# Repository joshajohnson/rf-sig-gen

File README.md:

# RF Signal Generator

## 23.5 - 6000 MHz MAX2871 based RF signal generator in an Adafruit Feather form factor.
- MAX2871 23.5 - 6000 MHz Fractional/Integer-N Synthesizer/VCO
- -35 to +15 dBm output power (-25 to +10 across entire frequency range)
- Output control within 0.5 dB, with closed loop feedback
- GUI allowing easy control, including sweep capabilities
- Adafruit Feather form factor
- Firmware works with my [STM32F103 Feather](https://github.com/joshajohnson/stm32f103-feather)

### TODO

#### Software
- [ ] Display not updating if time between frequency steps in sweep is too long (greater than UART timeout)
- [ ] Map keyboard to frequency and power adjustment in GUI
- [ ] CLI and GUI modes based on sys.argv **NOTE CLI works but is very finiky wrt command order and updating**
- [ ] Fractional vs Int N selection

#### Firmware
- [ ] Calibrate output power
- [ ] Rewrite with RTOS to ensure a more responsive user experience
- [ ] Add ability to select Frac / Int N PLL settings
- [ ] Dimmable LEDs

#### Hardware
- [ ] Many pin locations incorrect (SPI pins off by one...)
- [ ] LED's back to front, and connected to GND instead of VCC
- [ ] Feather footprint internal pin numbers incorrect

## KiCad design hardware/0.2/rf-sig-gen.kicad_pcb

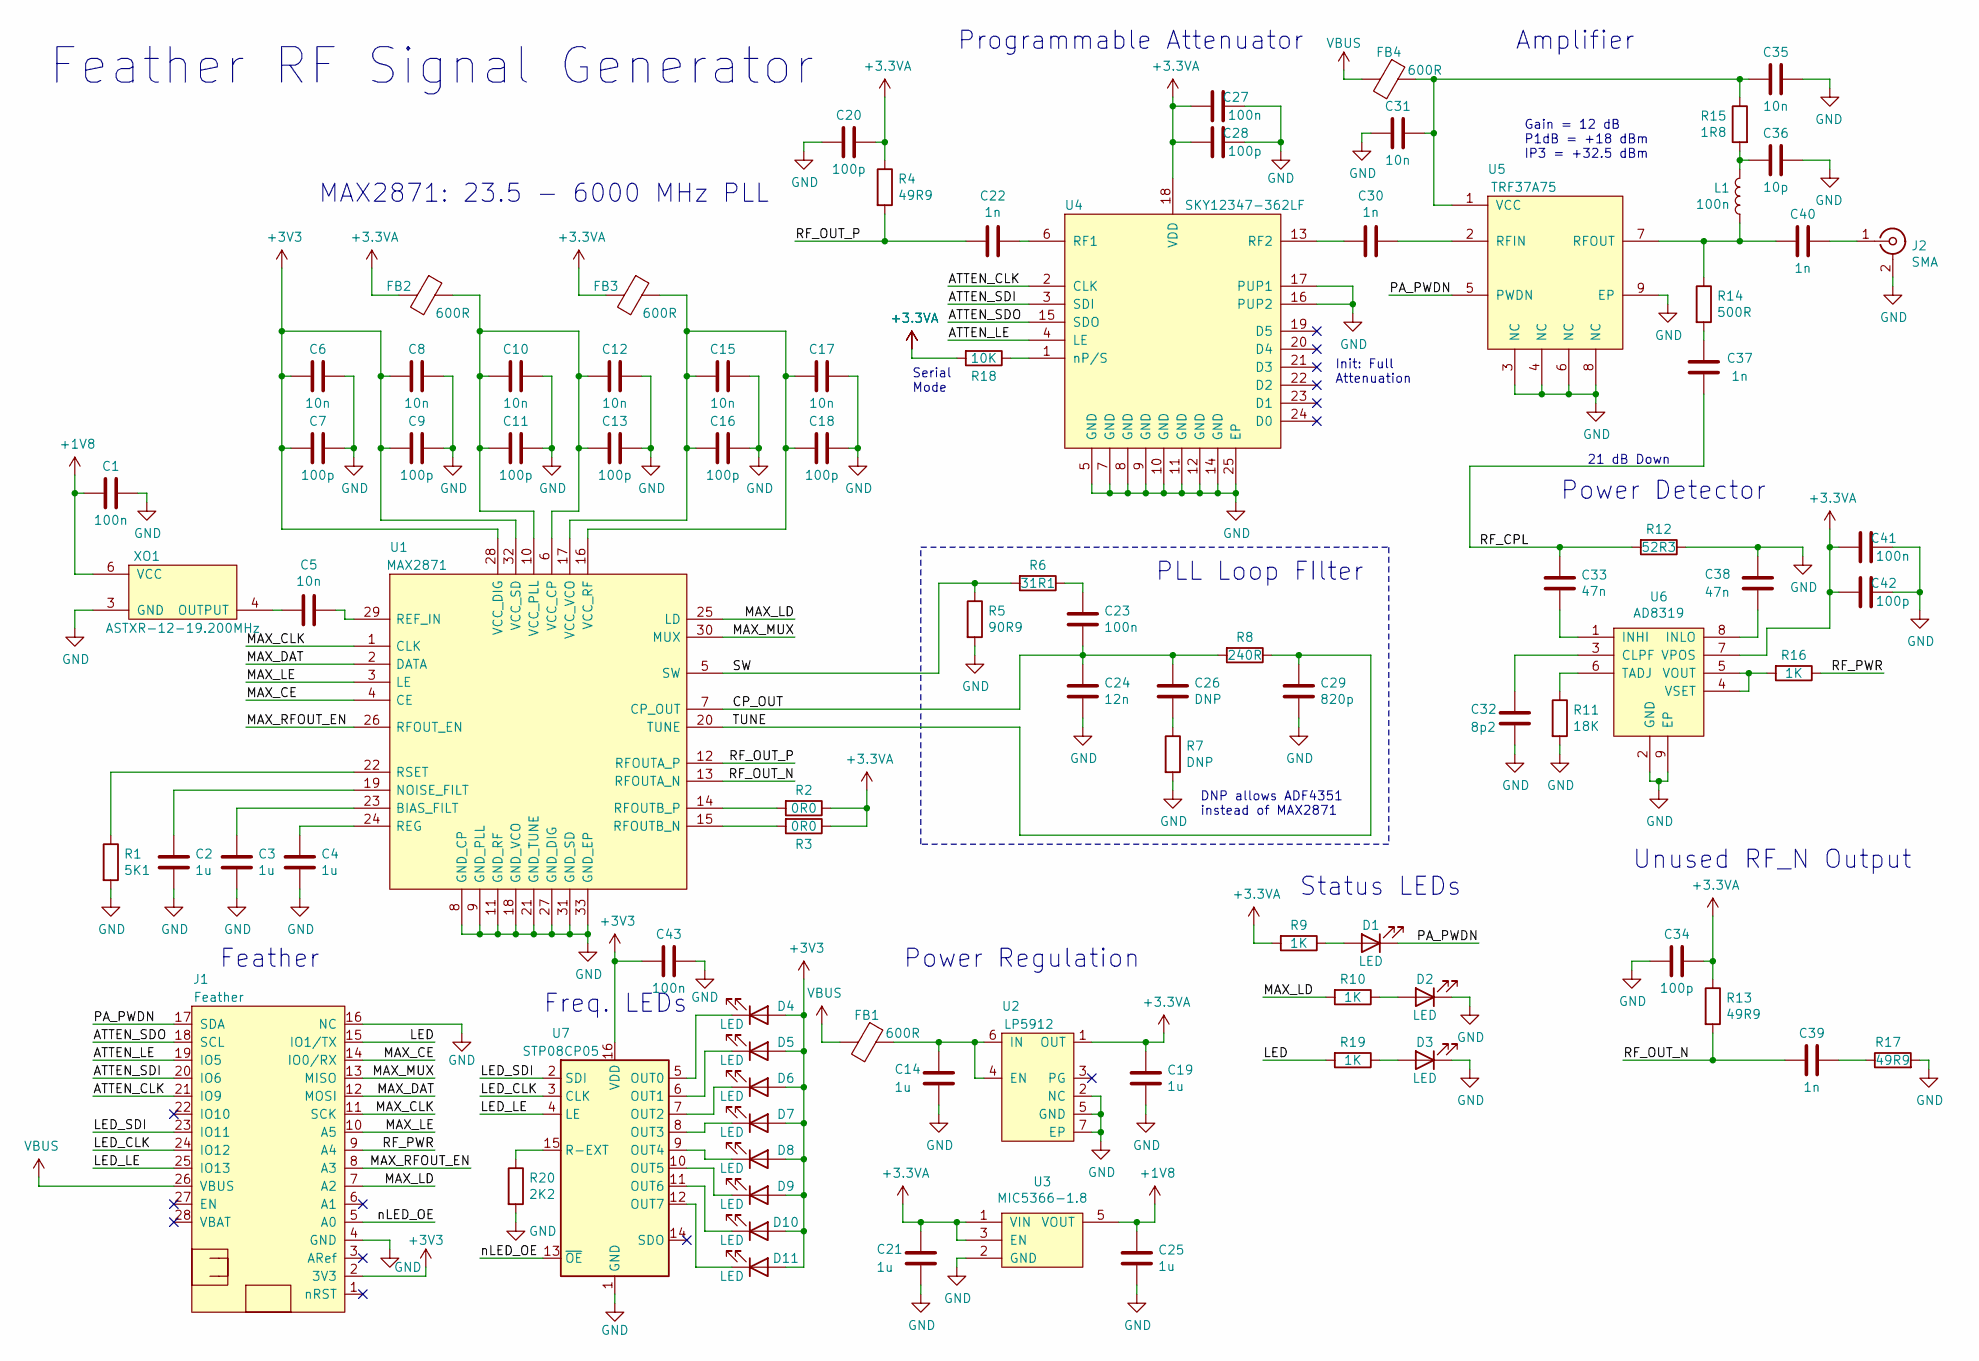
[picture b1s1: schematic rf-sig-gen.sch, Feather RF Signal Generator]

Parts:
C1, C23, C27, C41, C43: 100n; C_0402_1005Metric
C2, C3, C4, C14, C19, C21, C25: 1u; C_0402_1005Metric
C5, C6, C8, C10, C12, C15, C17, C31, C35: 10n; C_0402_1005Metric
C7, C9, C11, C13, C16, C18, C20, C28, C34, C42: 100p; C_0402_1005Metric
C22, C30, C37, C39, C40: 1n; C_0402_1005Metric
C24: 12n; C_0402_1005Metric
C26: DNP; C_0402_1005Metric
C29: 820p; C_0402_1005Metric
C32: 8p2; C_0402_1005Metric
C33, C38: 47n; C_0402_1005Metric
C36: 10p; C_0402_1005Metric
D1, D2, D3, D4, D5, D6, D7, D8, D9, D10, D11: LED; LED_0603_1608Metric_Castellated
FB1, FB2, FB3, FB4: 600R; Ferrite_Bead_0603
J1: Feather; featherwing-short
J2: SMA; SMA_EDGE_MOUNT_INSET
L1: 100n; L_0402_1005Metric
R1: 5K1; R_0402_1005Metric
R2, R3: 0R0; R_0402_1005Metric
R4, R13, R17: 49R9; R_0402_1005Metric
R5: 90R9; R_0402_1005Metric
R6: 31R1; R_0402_1005Metric
R7: DNP; R_0402_1005Metric
R8: 240R; R_0402_1005Metric
R9, R10, R16, R19: 1K; R_0402_1005Metric
R11: 18K; R_0402_1005Metric
R12: 52R3; R_0402_1005Metric
R14: 500R; R_0402_1005Metric
R15: 1R8; R_0402_1005Metric
R18: 10K; R_0402_1005Metric
R20: 2K2; R_0402_1005Metric
U1: MAX2871; QFN-32-1EP_5x5mm_Pitch0.5mm_Thermal_Vias; DigiKey MAX2871ETJ+TCT-ND
U2: LP5912; DFN-6-1EP_2x2mm_P0.65mm_EP1x1.6mm; DigiKey 296-44294-1-ND
U3: MIC5366-1.8; SOT-353_SC-70-5; DigiKey 576-3203-1-ND
U4: SKY12347-362LF; QFN-24-1EP_4x4mm_P0.5mm_EP2.7x2.7mm_ThermalVias; DigiKey 863-1298-1-ND
U5: TRF37A75; DFN-8-1EP_2x2mm_P0.5mm_EP0.9x1.5mm; DigiKey 296-37886-1-ND
U6: AD8319; DFN-8-1EP_2x3mm_P0.5mm_EP0.61x2.2mm; DigiKey AD8319ACPZ-R7CT-ND
U7: STP08CP05; TSSOP-16_4.4x5mm_P0.65mm; DigiKey 497-6269-1-ND
XO1: ASTXR-12-19.200MHz; ASTXR-12; DigiKey 535-12687-1-ND

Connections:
+1V8: C1.2, C25.1, U3.5 (VOUT), XO1.6 (VCC)
+3.3VA: C19.1, C20.1, C21.1, C27.2, C28.2, C34.1, C41.2, C42.2, FB2.2, FB3.2, R2.1, R3.1, R4.1, R9.2, R13.1, R18.2, U2.1 (OUT), U3.1 (VIN), U3.3 (EN), U4.18 (VDD), U6.7 (VPOS)
+3V3: C6.2, C7.2, C8.2, C9.2, C43.2, D4.2 (A), D5.2 (A), D6.2 (A), D7.2 (A), D8.2 (A), D9.2 (A), D10.2 (A), D11.2 (A), J1.2 (3V3), U1.28 (VCC_DIG), U1.32 (VCC_SD), U7.16 (VDD)
/ATTEN_CLK: J1.21 (IO9), U4.2 (CLK)
/ATTEN_LE: J1.19 (IO5), U4.4 (LE)
/ATTEN_SDI: J1.20 (IO6), U4.3 (SDI)
/ATTEN_SDO: J1.18 (SCL), U4.15 (SDO)
/CP_OUT: C23.2, C24.1, C26.1, R8.2, U1.7 (CP_OUT)
/LED: J1.15 (IO1/TX), R19.2
/LED_CLK: J1.24 (IO12), U7.3 (CLK)
/LED_LE: J1.25 (IO13), U7.4 (LE)
/LED_SDI: J1.23 (IO11), U7.2 (SDI)
/MAX_CE: J1.14 (IO0/RX), U1.4 (CE)
/MAX_CLK: J1.11 (SCK), U1.1 (CLK)
/MAX_DAT: J1.12 (MOSI), U1.2 (DATA)
/MAX_LD: J1.7 (A2), R10.2, U1.25 (LD)
/MAX_LE: J1.10 (A5), U1.3 (LE)
/MAX_MUX: J1.13 (MISO), U1.30 (MUX)
/MAX_RFOUT_EN: J1.8 (A3), U1.26 (RFOUT_EN)
/PA_PWDN: D1.1 (K), J1.17 (SDA), U5.5 (PWDN)
/RF_CPL: C33.1, C37.2, R12.2
/RF_OUT_N: C39.2, R13.2, U1.13 (RFOUTA_N)
/RF_OUT_P: C22.2, R4.2, U1.12 (RFOUTA_P)
/RF_PWR: J1.9 (A4), R16.1
/SW: R5.1, R6.2, U1.5 (SW)
/TUNE: C29.1, R8.1, U1.20 (TUNE)
/nLED_OE: J1.5 (A0), U7.13 (~OE)
GND: C1.1, C2.2, C3.2, C4.2, C6.1, C7.1, C8.1, C9.1, C10.1, C11.1, C12.1, C13.1, C14.2, C15.1, C16.1, C17.1, C18.1, C19.2, C20.2, C21.2, C24.2, C25.2, C27.1, C28.1, C29.2, C31.2, C32.2, C34.2, C35.2, C36.2, C38.1, C41.1, C42.1, C43.1, D2.1 (K), D3.1 (K), J1.4 (GND), J1.16 (NC), J2.2 (Ext), R1.2, R5.2, R7.2, R11.2, R12.1, R17.2, R20.2, U1.8 (GND_CP), U1.9 (GND_PLL), U1.11 (GND_RF), U1.18 (GND_VCO), U1.21 (GND_TUNE), U1.27 (GND_DIG), U1.31 (GND_SD), U1.33 (GND_EP), U2.2 (NC), U2.5 (GND), U2.7 (EP), U3.2 (GND), U4.5 (GND), U4.7 (GND), U4.8 (GND), U4.9 (GND), U4.10 (GND), U4.11 (GND), U4.12 (GND), U4.14 (GND), U4.16 (PUP2), U4.17 (PUP1), U4.25 (EP), U5.3 (NC), U5.4 (NC), U5.6 (NC), U5.8 (NC), U5.9 (EP), U6.2 (GND), U6.9 (EP), U7.1 (GND), XO1.3 (GND)
unnamed: C2.1, U1.19 (NOISE_FILT)
unnamed: C3.1, U1.23 (BIAS_FILT)
unnamed: C4.1, U1.24 (REG)
unnamed: C5.1, U1.29 (REF_IN)
unnamed: C5.2, XO1.4 (OUTPUT)
unnamed: C10.2, C11.2, C12.2, C13.2, FB2.1, U1.6 (VCC_CP), U1.10 (VCC_PLL)
unnamed: C14.1, FB1.1, U2.4 (EN), U2.6 (IN)
unnamed: C15.2, C16.2, C17.2, C18.2, FB3.1, U1.16 (VCC_RF), U1.17 (VCC_VCO)
unnamed: C22.1, U4.6 (RF1)
unnamed: C23.1, R6.1
unnamed: C26.2, R7.1
unnamed: C30.1, U5.2 (RFIN)
unnamed: C30.2, U4.13 (RF2)
unnamed: C31.1, C35.1, FB4.1, R15.1, U5.1 (VCC)
unnamed: C32.1, U6.3 (CLPF)
unnamed: C33.2, U6.1 (INHI)
unnamed: C36.1, L1.1, R15.2
unnamed: C37.1, R14.2
unnamed: C38.2, U6.8 (INLO)
unnamed: C39.1, R17.1
unnamed: C40.1, J2.1 (In)
unnamed: C40.2, L1.2, R14.1, U5.7 (RFOUT)
unnamed: D1.2 (A), R9.1
unnamed: D2.2 (A), R10.1
unnamed: D3.2 (A), R19.1
unnamed: D4.1 (K), U7.5 (OUT0)
unnamed: D5.1 (K), U7.6 (OUT1)
unnamed: D6.1 (K), U7.7 (OUT2)
unnamed: D7.1 (K), U7.8 (OUT3)
unnamed: D8.1 (K), U7.9 (OUT4)
unnamed: D9.1 (K), U7.10 (OUT5)
unnamed: D10.1 (K), U7.11 (OUT6)
unnamed: D11.1 (K), U7.12 (OUT7)
unnamed: R1.1, U1.22 (RSET)
unnamed: R2.2, U1.14 (RFOUTB_P)
unnamed: R3.2, U1.15 (RFOUTB_N)
unnamed: R11.1, U6.6 (TADJ)
unnamed: R16.2, U6.4 (VSET), U6.5 (VOUT)
unnamed: R18.1, U4.1 (nP/S)
unnamed: R20.1, U7.15 (R-EXT)
VBUS: FB1.2, FB4.2, J1.26 (VBUS)

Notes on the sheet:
MAX2871: 23.5 - 6000 MHz PLL
PLL Loop FIlter
DNP allows ADF4351 instead of MAX2871
Unused RF_N Output
Serial Mode
Init: Full Attenuation
Programmable Attenuator
Feather RF Signal Generator
Amplifier
Gain = 12 dB P1dB = +18 dBm IP3 = +32.5 dBm
Power Detector
21 dB Down
Power Regulation
Status LEDs
Freq. LEDs
Feather

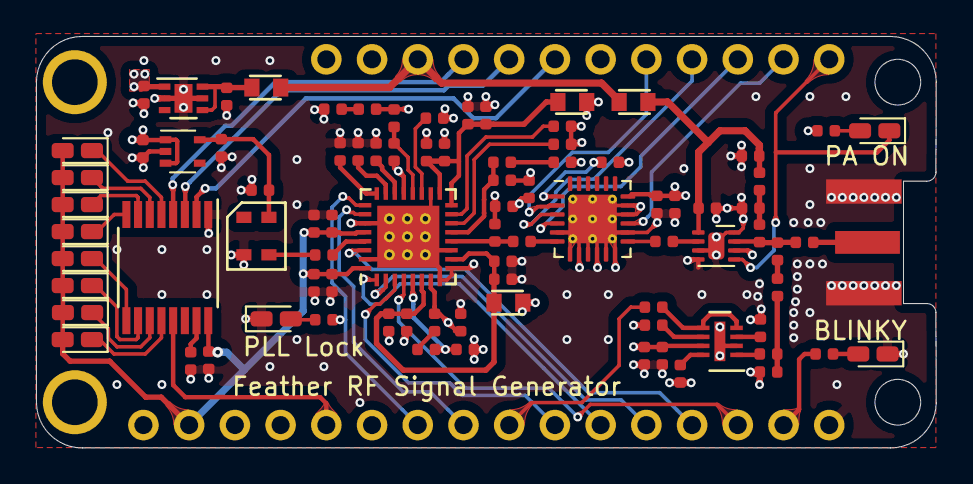
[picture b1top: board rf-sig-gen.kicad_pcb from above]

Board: 4 copper layers, 50.0 x 22.9 mm, 89 parts (0 on the bottom side), 69 nets.

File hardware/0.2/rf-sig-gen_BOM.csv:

"Qty","Reference(s)","Value","Footprint","MPN","DigiKey","LCSC","Manufacturer","DNP","Notes"
"5","C1, C23, C27, C41, C43","100n","Capacitor_SMD:C_0402_1005Metric","","","","","",""
"9","C10, C12, C15, C17, C31, C35, C5, C6, C8","10n","Capacitor_SMD:C_0402_1005Metric","","","","","",""
"10","C11, C13, C16, C18, C20, C28, C34, C42, C7, C9","100p","Capacitor_SMD:C_0402_1005Metric","","","","","",""
"7","C14, C19, C2, C21, C25, C3, C4","1u","Capacitor_SMD:C_0402_1005Metric","","","","","",""
"5","C22, C30, C37, C39, C40","1n","Capacitor_SMD:C_0402_1005Metric","","","","","",""
"1","C24","12n","Capacitor_SMD:C_0402_1005Metric","","","","","",""
"1","C26","DNP","Capacitor_SMD:C_0402_1005Metric","","","","","",""
"1","C29","820p","Capacitor_SMD:C_0402_1005Metric","","","","","",""
"1","C32","8p2","Capacitor_SMD:C_0402_1005Metric","","","","","",""
"2","C33, C38","47n","Capacitor_SMD:C_0402_1005Metric","","","","","",""
"1","C36","10p","Capacitor_SMD:C_0402_1005Metric","","","","","",""
"11","D1, D10, D11, D2, D3, D4, D5, D6, D7, D8, D9","LED","LED_SMD:LED_0603_1608Metric_Castellated","","","","","",""
"4","FB1, FB2, FB3, FB4","600R","josh-passives-smt:Ferrite_Bead_0603","","","","","",""
"1","J1","Feather","josh-connectors:featherwing-short","","","","","",""
"1","J2","SMA","josh-connectors:SMA_EDGE_MOUNT_INSET","","","","","",""
"1","L1","100n","Inductor_SMD:L_0402_1005Metric","","","","","",""
"1","R1","5K1","Resistor_SMD:R_0402_1005Metric","","","","","",""
"4","R10, R16, R19, R9","1K","Resistor_SMD:R_0402_1005Metric","","","","","",""
"1","R11","18K","Resistor_SMD:R_0402_1005Metric","","","","","",""
"1","R12","52R3","Resistor_SMD:R_0402_1005Metric","","","","","",""
"3","R13, R17, R4","49R9","Resistor_SMD:R_0402_1005Metric","","","","","",""
"1","R14","500R","Resistor_SMD:R_0402_1005Metric","","","","","",""
"1","R15","1R8","Resistor_SMD:R_0402_1005Metric","","","","","",""
"1","R18","10K","Resistor_SMD:R_0402_1005Metric","","","","","",""
"2","R2, R3","0R0","Resistor_SMD:R_0402_1005Metric","","","","","",""
"1","R20","2K2","Resistor_SMD:R_0402_1005Metric","","","","","",""
"1","R5","90R9","Resistor_SMD:R_0402_1005Metric","","","","","",""
"1","R6","31R1","Resistor_SMD:R_0402_1005Metric","","","","","",""
"1","R7","DNP","Resistor_SMD:R_0402_1005Metric","","","","","",""
"1","R8","240R","Resistor_SMD:R_0402_1005Metric","","","","","",""
"1","U1","MAX2871","josh-dfn-qfn:QFN-32-1EP_5x5mm_Pitch0.5mm_Thermal_Vias","","MAX2871ETJ+TCT-ND ","","","",""
"1","U2","LP5912","Package_DFN_QFN:DFN-6-1EP_2x2mm_P0.65mm_EP1x1.6mm","","296-44294-1-ND","","","",""
"1","U3","MIC5366-1.8","Package_TO_SOT_SMD:SOT-353_SC-70-5","","576-3203-1-ND","","","",""
"1","U4","SKY12347-362LF","Package_DFN_QFN:QFN-24-1EP_4x4mm_P0.5mm_EP2.7x2.7mm_ThermalVias","","863-1298-1-ND","","","",""
"1","U5","TRF37A75","Package_DFN_QFN:DFN-8-1EP_2x2mm_P0.5mm_EP0.9x1.5mm","","296-37886-1-ND","","","",""
"1","U6","AD8319","Package_DFN_QFN:DFN-8-1EP_2x3mm_P0.5mm_EP0.61x2.2mm","","AD8319ACPZ-R7CT-ND ","","","",""
"1","U7","STP08CP05","Package_SO:TSSOP-16_4.4x5mm_P0.65mm","","497-6269-1-ND","","","",""
"1","XO1","ASTXR-12-19.200MHz","josh-oscillators:ASTXR-12","","535-12687-1-ND","","","",""

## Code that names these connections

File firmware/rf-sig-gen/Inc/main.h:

/* USER CODE BEGIN Header */
/**
  ******************************************************************************
  * @file           : main.h
  * @brief          : Header for main.c file.
  *                   This file contains the common defines of the application.
  ******************************************************************************
  * @attention
  *
  * <h2><center>&copy; Copyright (c) 2020 STMicroelectronics.
  * All rights reserved.</center></h2>
  *
  * This software component is licensed by ST under BSD 3-Clause license,
  * the "License"; You may not use this file except in compliance with the
  * License. You may obtain a copy of the License at:
  *                        opensource.org/licenses/BSD-3-Clause
  *
  ******************************************************************************
  */
/* USER CODE END Header */

/* Define to prevent recursive inclusion -------------------------------------*/
#ifndef __MAIN_H
#define __MAIN_H

#ifdef __cplusplus
extern "C" {
#endif

/* Includes ------------------------------------------------------------------*/
#include "stm32f1xx_hal.h"

/* Private includes ----------------------------------------------------------*/
/* USER CODE BEGIN Includes */

/* USER CODE END Includes */

/* Exported types ------------------------------------------------------------*/
/* USER CODE BEGIN ET */
#define  FIFO_SIZE 128  // must be 2^N
typedef struct FIFO
{
	uint32_t head;
	uint32_t tail;
	uint8_t data[FIFO_SIZE];
	uint8_t dataReady;
	uint8_t charArray[FIFO_SIZE];
} FIFO;

extern FIFO RX_FIFO;
/* USER CODE END ET */

/* Exported constants --------------------------------------------------------*/
/* USER CODE BEGIN EC */
#define FRAC_N 		0
#define INT_N		1

#define nVERBOSE 	0
#define VERBOSE 	1
/* USER CODE END EC */

/* Exported macro ------------------------------------------------------------*/
/* USER CODE BEGIN EM */
#define  FIFO_INCR(x) (((x)+1)&((FIFO_SIZE)-1))
/* USER CODE END EM */

/* Exported functions prototypes ---------------------------------------------*/
void Error_Handler(void);

/* USER CODE BEGIN EFP */

/* USER CODE END EFP */

/* Private defines -----------------------------------------------------------*/
#define MAX_LE_Pin GPIO_PIN_1
#define MAX_LE_GPIO_Port GPIOA
#define MAX_RFOUT_EN_Pin GPIO_PIN_2
#define MAX_RFOUT_EN_GPIO_Port GPIOA
#define MAX_LD_Pin GPIO_PIN_3
#define MAX_LD_GPIO_Port GPIOA
#define nLED_OE_Pin GPIO_PIN_5
#define nLED_OE_GPIO_Port GPIOA
#define ATTEN_LE_Pin GPIO_PIN_6
#define ATTEN_LE_GPIO_Port GPIOA
#define ATTEN_SDO_Pin GPIO_PIN_7
#define ATTEN_SDO_GPIO_Port GPIOA
#define ATTEN_CLK_Pin GPIO_PIN_0
#define ATTEN_CLK_GPIO_Port GPIOB
#define LED_SDI_Pin GPIO_PIN_10
#define LED_SDI_GPIO_Port GPIOB
#define LED_CLK_Pin GPIO_PIN_11
#define LED_CLK_GPIO_Port GPIOB
#define LED_LE_Pin GPIO_PIN_12
#define LED_LE_GPIO_Port GPIOB
#define nLED_RED_Pin GPIO_PIN_13
#define nLED_RED_GPIO_Port GPIOB
#define nLED_GRN_Pin GPIO_PIN_14
#define nLED_GRN_GPIO_Port GPIOB
#define nLED_BLU_Pin GPIO_PIN_15
#define nLED_BLU_GPIO_Port GPIOB
#define nLED_USR_Pin GPIO_PIN_8
#define nLED_USR_GPIO_Port GPIOA
#define SWDIO_Pin GPIO_PIN_13
#define SWDIO_GPIO_Port GPIOA
#define SWDCLK_Pin GPIO_PIN_14
#define SWDCLK_GPIO_Port GPIOA
#define USB_PU_Pin GPIO_PIN_15
#define USB_PU_GPIO_Port GPIOA
#define MAX_CE_Pin GPIO_PIN_3
#define MAX_CE_GPIO_Port GPIOB
#define MAX_DAT_Pin GPIO_PIN_4
#define MAX_DAT_GPIO_Port GPIOB
#define MAX_CLK_Pin GPIO_PIN_5
#define MAX_CLK_GPIO_Port GPIOB
#define LED_Pin GPIO_PIN_6
#define LED_GPIO_Port GPIOB
#define MAX_MUX_Pin GPIO_PIN_7
#define MAX_MUX_GPIO_Port GPIOB
#define ATTEN_SDI_Pin GPIO_PIN_8
#define ATTEN_SDI_GPIO_Port GPIOB
#define PA_PWDN_Pin GPIO_PIN_9
#define PA_PWDN_GPIO_Port GPIOB
/* USER CODE BEGIN Private defines */

/* USER CODE END Private defines */

#ifdef __cplusplus
}
#endif

#endif /* __MAIN_H */

/************************ (C) COPYRIGHT STMicroelectronics *****END OF FILE****/

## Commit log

2019-11-20 add KiCad files
2019-11-21 update schematic
2019-12-17 more progress
2019-12-18 final changes
2020-04-27 add gitignore
2020-04-27 move to correct repo
2020-04-27 com port comms working
2020-04-27 mostly working
2020-04-27 console progress
2020-04-27 tx text changes
2020-05-03 qui working!
2020-05-03 firmware to support gui
2020-05-09 resolving gui bugs
2020-05-09 more bug hunting
2020-05-09 bug squashing and improvment for gui
2020-05-09 serial port issues + max attenuation on startup
2020-05-10 fix attenuation bugs
2020-05-10 bug hunting
2020-05-10 add readme
2020-05-10 cleaning up repo
2020-05-10 add gui image
2020-05-10 Create LICENSE
2020-05-10 Create LICENCE-HW
2020-05-10 update license
2020-05-10 building with -wall
2020-05-16 sw and readme updates
2020-05-16 adding features / bug hunting
2020-05-30 r0.2
